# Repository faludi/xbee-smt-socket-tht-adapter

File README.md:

# xbee-smt-socket-tht-adapter
XBee SMT Socket -> THT Adapter

This is a small adapter that reversibly installs a surface-mount XBee in place of a through-hole XBee. This means that modules like Digi's XBee 868LP that only come in a SMT version can be mounted on an XBee standard THT footprint without needing to permanently solder anything. The SMT XBee had to be rotated 90º so that its footprint does not conflict with the THT footprint underneath. All 20 pin connections have been tested and function as expected.

This adapter uses Digi's custom spring socket (part <a href="http://www.digikey.com/product-search/en?keywords=76002056">76002056</a>) as well as two sets of 10 pin, 2mm SMD connection headers. These <a href="http://www.digikey.com/product-search/en?keywords=SAM1172-11-nd">11-pin break-away headers</a> work well, just be sure to break off the extra left-facing pin.

Printed circuit boards can be ordered from <a href="https://oshpark.com/shared_projects/7I4gdVdC">OSH Park</a>.

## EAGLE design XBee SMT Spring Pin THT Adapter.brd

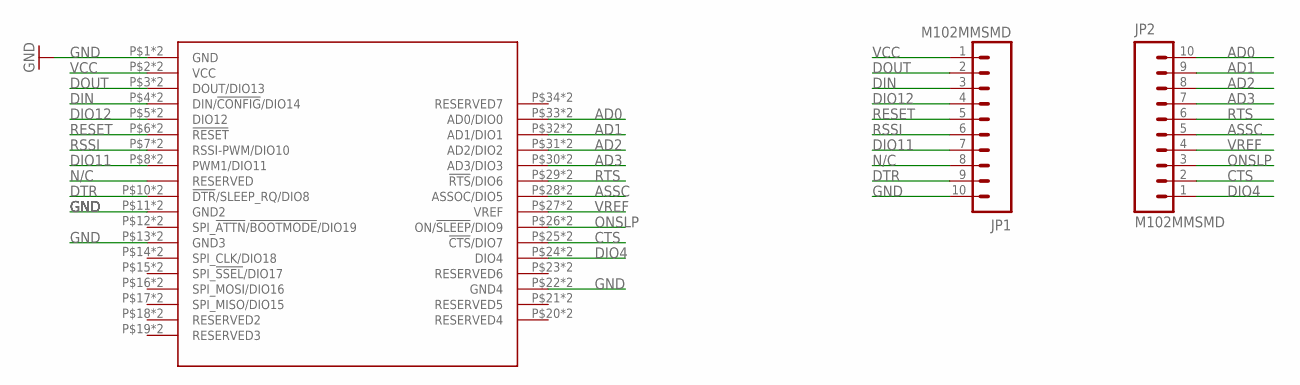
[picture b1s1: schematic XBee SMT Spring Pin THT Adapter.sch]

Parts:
JP1, JP2: M102MMSMD; 1X10-2MM-SMD
U$2: XBEE-SMT; XBEE_SMT_SPRING_SOCKET_SMALL_HOLE_76002056

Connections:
AD0: JP2.10, U$2.P$33 (AD0/DIO0), U$2.P$330 (AD0/DIO0)
AD1: JP2.9, U$2.P$32 (AD1/DIO1), U$2.P$320 (AD1/DIO1)
AD2: JP2.8, U$2.P$31 (AD2/DIO2), U$2.P$310 (AD2/DIO2)
AD3: JP2.7, U$2.P$30 (AD3/DIO3), U$2.P$300 (AD3/DIO3)
ASSC: JP2.5, U$2.P$28 (ASSOC/DIO5), U$2.P$280 (ASSOC/DIO5)
CTS: JP2.2, U$2.P$25 (!CTS!/DIO7), U$2.P$250 (!CTS!/DIO7)
DIN: JP1.3, U$2.P$4 (DIN/!CONFIG!/DIO14), U$2.P$040 (DIN/!CONFIG!/DIO14)
DIO4: JP2.1, U$2.P$24 (DIO4), U$2.P$240 (DIO4)
DIO11: JP1.7, U$2.P$8 (PWM1/DIO11), U$2.P$080 (PWM1/DIO11)
DIO12: JP1.4, U$2.P$5 (DIO12), U$2.P$050 (DIO12)
DOUT: JP1.2, U$2.P$3 (DOUT/DIO13), U$2.P$030 (DOUT/DIO13)
DTR: JP1.9, U$2.P$10 (!DTR!/SLEEP_RQ/DIO8), U$2.P$100 (!DTR!/SLEEP_RQ/DIO8)
GND: JP1.10, U$2.P$1 (GND), U$2.P$010 (GND), U$2.P$11 (GND2), U$2.P$13 (GND3), U$2.P$22 (GND4), U$2.P$110 (GND2), U$2.P$130 (GND3), U$2.P$220 (GND4)
N/C: JP1.8, U$2.P$9 (RESERVED), U$2.P$090 (RESERVED)
ONSLP: JP2.3, U$2.P$26 (ON/!SLEEP!/DIO9), U$2.P$260 (ON/!SLEEP!/DIO9)
RESET: JP1.5, U$2.P$6 (!RESET), U$2.P$060 (!RESET)
RSSI: JP1.6, U$2.P$7 (RSSI-PWM/DIO10), U$2.P$070 (RSSI-PWM/DIO10)
RTS: JP2.6, U$2.P$29 (!RTS!/DIO6), U$2.P$290 (!RTS!/DIO6)
VCC: JP1.1, U$2.P$2 (VCC), U$2.P$020 (VCC)
VREF: JP2.4, U$2.P$27 (VREF), U$2.P$270 (VREF)

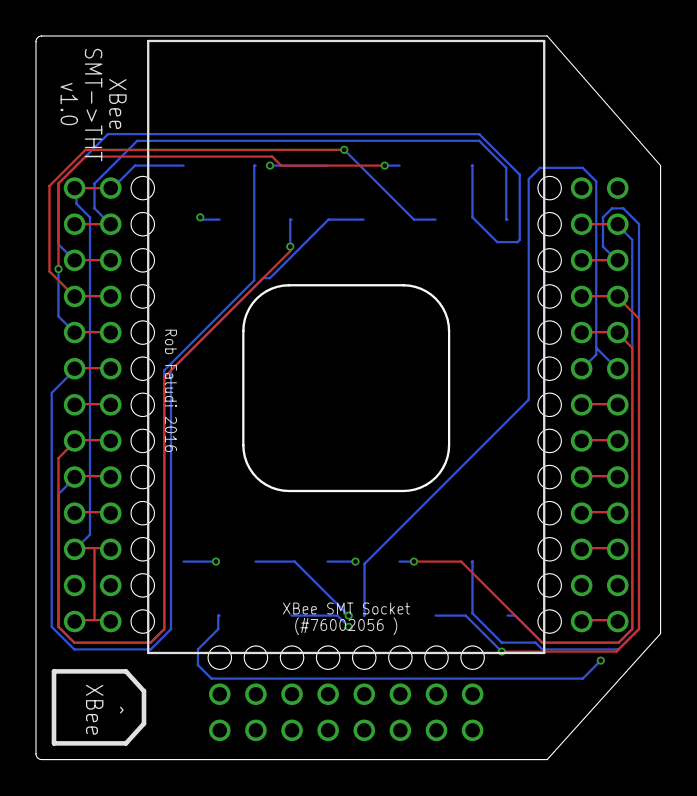
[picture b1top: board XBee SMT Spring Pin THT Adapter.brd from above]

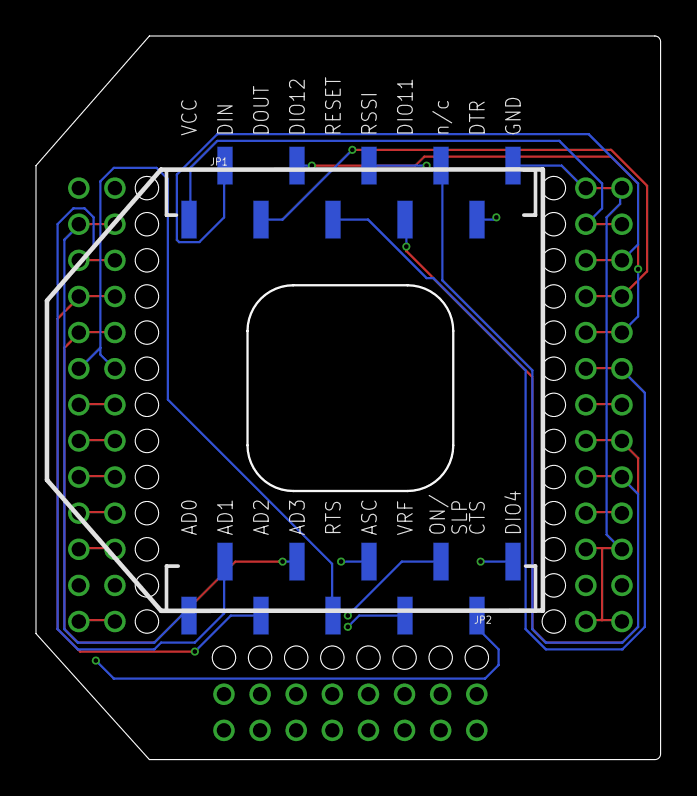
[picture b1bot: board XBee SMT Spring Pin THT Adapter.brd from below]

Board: 4 copper layers, 34.6 x 40.1 mm, 3 parts (2 on the bottom side), 20 nets.

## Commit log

2016-04-07 Schematic in PDF format
2016-04-07 Board layout in PDF format
2016-04-07 Eagle CAD design files
2016-04-07 project description and parts

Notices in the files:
parts and their libraries:
SparkFun-Connectors: Licensing: CC v3.0 Share-Alike You are welcome to use this library for commercial purposes.
